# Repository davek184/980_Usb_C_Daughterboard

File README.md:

Replacement USB-C daughterboard for Leopold FC980c/FC980m, can be used with the stock case or Norbauer Heavy-9.

Uses Qwiic / JST SH or Pico-EZmate connector.

_Note stock Leopold case requires filing USB opening and cable is tight._

Related project [FC980c controller](https://github.com/davek184/fc980c-controller)

## Revision 1.3
- Added Molex Pico-Ezmate connector option.  Note there are 2 of these one on the back that is optional.

## BOM

| LCSC part # | Description   | Value | Package  | Amount |
| ----------- | ------------- | ----- | -------- | ------:|
| C165948     | USB           |       | SMD/TH   | 1      |
| C160404     | Connector     |       | SMD      | 1      |
| C528030     | Connector     |       | SMD      | 1      |
| C261942     | Fuse	      |       | SMD      | 1      |
| C27834      | Resistor      | 5.1   | SMD      | 2      |
| C7519       | ESD           |       | SMD      | 1      |
| C528030     | Connector     |       | SMD      | 2      | 

## Cable

This daughterboard uses a different connector then the OEM one. Suggest starting with an [Adafruit 4424 cable](https://www.adafruit.com/product/4424) so no crimping needs to be done.

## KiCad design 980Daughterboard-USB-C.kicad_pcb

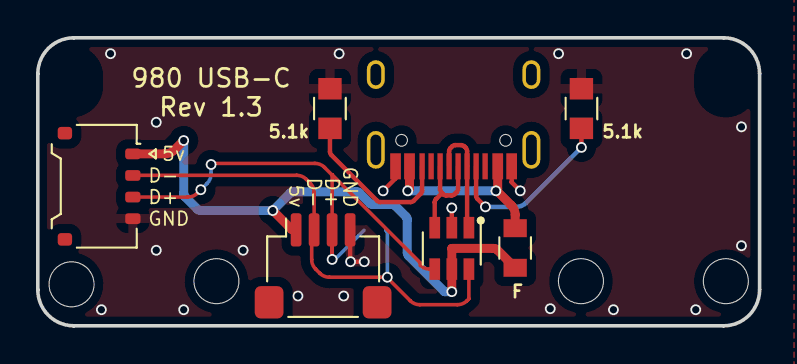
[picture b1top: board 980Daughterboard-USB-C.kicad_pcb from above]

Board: 2 copper layers, 40.1 x 16.0 mm, 8 parts (1 on the bottom side), 8 nets.

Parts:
F: Polyfuse_Small; F_0805
J1: TYPE-C-31-M-12; HRO-TYPE-C-31-M-12
J2: ai03_ud; JST_SH_SM04B-SRSS-TB_1x04-1MP_P1.00mm_Horizontal
J3, J4: Molex_Pico-EZmate_78171-0004_1x04-1MP_P1.20mm_Ver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; Molex_Pico-EZmate_78171-0004_1x04-1MP_P1.20mm_Vertical
R1, R2: 5.1k; R_0805
U1: USBLC6-2SC6

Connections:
D+: J2.3, J3.3, J4.3, U1.4 (I/O2)
D-: J2.2, J3.2, J4.2, U1.6 (I/O1)
GND: J1.1 (GND), J1.12 (GND), J2.4, J3.4, J4.4, R1.2, R2.2, U1.2 (GND)
unnamed: J1.4 (CC1), R2.1
unnamed: J1.5 (DN2), J1.7 (DN1), U1.1 (I/O1)
unnamed: J1.6 (DP1), J1.8 (DP2), U1.3 (I/O2)
unnamed: J1.10 (CC2), R1.1
VBUS: F.1, F.2, J1.2 (VBUS), J1.11 (VBUS), J2.1, J3.1, J4.1, U1.5 (VBUS)

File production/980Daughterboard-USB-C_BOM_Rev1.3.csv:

Designator,Footprint,Quantity,Value,LCSC Part #
F,F_0805,1,Polyfuse_Small,C261942
J1,HRO-TYPE-C-31-M-12,1,TYPE-C-31-M-12,C165948
J2,JST_SH_SM04B-SRSS-TB_1x04-1MP_P1.00mm_Horizontal,1,ai03_ud,C160404
"J3, J4",Molex_Pico-EZmate_78171-0004_1x04-1MP_P1.20mm_Vertical,2,Molex_Pico-EZmate_78171-0004_1x04-1MP_P1.20mm_Vertical,C528030
"R1, R2",R_0805,2,5.1k,C27834
U1,USBLC6-2SC6,1,USBLC6-2SC6,C7519

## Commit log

2023-02-25 Rev 1.3
    1.3 includes pico ezmate connector. There is also an additional connector on the back for the stock case.
2023-03-20 Version1.3
2024-08-10 Alt option from Tinster4x4
